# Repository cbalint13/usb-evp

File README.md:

# usb-evp
**USB Event Packet** protocol (LoRA) Stick

Original project dating back @ 2018 [CircuitMaker USB-EVP-LoRa](https://workspace.circuitmaker.com/Projects/Details/Cristian-Balint/USB-EVP-LoRa)

## Description

USB stick for **Event Packet** (over LoRa) with integrated antenna on ISM 868/915 bands.

Exposes a generic USB HID interface by MCP2210 directly enabling OS & driver agnostic access from userland.

It have a minimal BOM (bill of materials).

## Specs:

* **Smallest LoRa stick** on the market by 1.6 x 4 cm
* Uses FCC and CE **certified** 100mW NiceRF module
* Own **ceramic micro-antenna** (VNA proved RF) for ISM band
* **OS agnostic**, opensource USB stack for windows, linux, android etc
* **C / C++** frontend with various examples
* May support **LPWAN networking** (IPv6 over 802.15.4 mac layer), with third party kernel module

Can be used in any USB port realying packets over the air.

## EU ISM band usage 
* [LoRa 868Mhz bands diagram](docs/legal)

## Design files
* See the [design files](hardware) available for Altium ®, CircuitMaker ®, KiCAD and Gerber format.
* Check [schematic](hardware/USB-eVo_v1.1.pdf) available as quick readable format.
* There is also an CircuitMaker ® [online version](https://circuitmaker.com/Projects/Details/Cristian-Balint/USB-EVP-LoRa) available.

## Software support
* See [software](software) section for configuration and support.

    ```
    $ ./bin/lora-receive /dev/hidraw4 
    LoRa RX count #1 frame length = 14 rssi = -61 dB snr = 8 dB
    0x00000000 20 6C 6F 72 61 20 6D 65  73 73 61 67 65 00 |  A lora message.
    ```

## Board images

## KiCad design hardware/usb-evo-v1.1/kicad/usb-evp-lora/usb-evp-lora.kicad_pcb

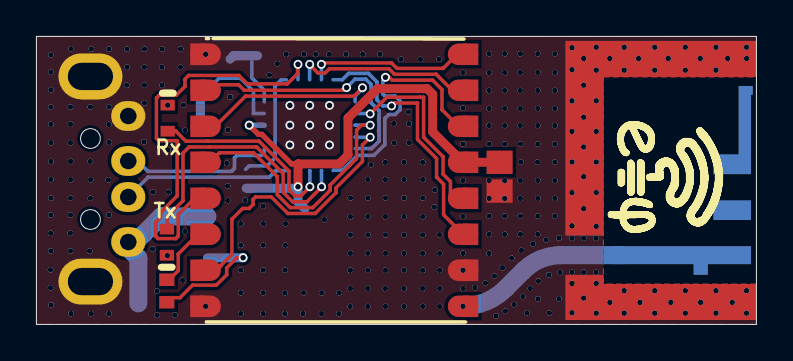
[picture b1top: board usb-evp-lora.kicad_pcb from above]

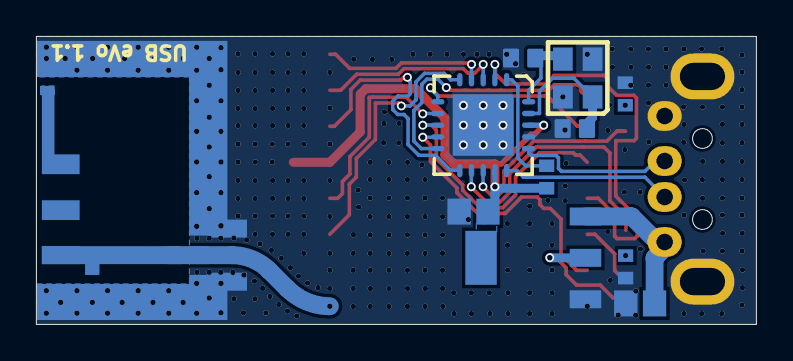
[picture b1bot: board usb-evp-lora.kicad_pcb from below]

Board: 2 copper layers, 40.0 x 16.0 mm, 20 parts (14 on the bottom side), 25 nets.

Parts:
A1: 868/915 Mhz; M620720
C1, C3, C4: 100nF; CAPC2013X88X50NL20T25
Ct1: 47pF; SMD0402
Ct2: 6.7pF; SMD0402
Cx1, Cx2: 30pF; PCB-EK4STCKT8HTL49C36KEC-1
DS1, DS2: LED-0603; VISH-TLMX1100-2_V
K1: USB-A; USB-A-H
R1, R2, R4, R5: 2k2; RESC1608X55X30LL15T15
U1: MCP2210; QFN-MQ20_N
U2: LoRa1276-C1; PCB-A2VA5FQQIKHNLZOD9I25-1
U3: AMS1117-3.3; MP04A_N
X1: 12Mhz; PCB-O7TDNPTWBJGDFBSKC48Q-1
uFL1: 50ohm; HRS-U.FL-R-SMT_V

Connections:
3.3V: C1.2, C3.2, R1.1, R2.1, U1.14, U1.18, U2.13, U3.2
GND: A1.GND, C1.1, C3.1, C4.1, Ct1.2, Ct2.1, Cx1.1, Cx2.1, K1.4, K1.5, R4.2, R5.2, U1.17, U1.21, U2.1, U2.8, U2.10, U3.1, X1.2, X1.4, uFL1.1, uFL1.2
NetA1_1: A1.1, Ct1.1, U2.9, uFL1.3
NetA1_2: A1.2, Ct2.2
NetC4_2: C4.2, K1.1, U3.3
NetCx1_2: Cx1.2, U1.20, X1.3
NetCx2_2: Cx2.2, U1.19, X1.1
NetDS1_1: DS1.1, U1.12
NetDS1_2: DS1.2, R4.1
NetDS2_1: DS2.1, U1.13
NetDS2_2: DS2.2, R5.1
NetK1_2: K1.2, U1.15
NetK1_3: K1.3, U1.16
NetR1_2: R1.2, U2.6
NetR2_2: R2.2, U1.1
NetU1_2: U1.2, U2.5
NetU1_3: U1.3, U2.15
NetU1_4: U1.4, U2.16
NetU1_5: U1.5, U2.11
NetU1_6: U1.6, U2.3
NetU1_7: U1.7, U2.12
NetU1_8: U1.8, U2.4
NetU1_9: U1.9, U2.7
NetU1_10: U1.10, U2.2
NetU1_11: U1.11, U2.14

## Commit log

2021-11-14 Publish hardware.
2021-12-21 Add SCH preview.
2021-12-21 Replace preview SCH with KiCAD one.
2024-03-16 Add EU license frequency band diagrams
2024-03-16 Export grraph as png variant
2024-03-24 Publish more ISM bands
2024-05-30 Release library and application examples
2024-05-30 Update rssi calculation for all bands
2024-05-31 Update argument passing in lora-receive
